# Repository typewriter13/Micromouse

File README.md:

# Micromouse

MicroMouse is a small autonomous robot designed to navigate and solve a maze completely on its own.

## About The Project

Our project is about a wall-following micromouse robot built on ESP32-S3, using IR proximity sensors for wall-centering and junction detection, a VL53L0X ToF sensor for front-wall stopping, quadrature encoders for wheel feedback, and a WiFi-based web UI for live tuning of PID gains, thresholds, and duty cycle limits.

https://github.com/user-attachments/assets/4806b698-6c4b-4d95-9de0-e866a1863b37

## Project Overview

### Hardware Used
- 1x ESP32-S3
- 1x DRV8833 Motor Driver
- 1x AMS1117 LDO
- 1x TPS54302 Buck Converter
- 2x DC encoder Motors
- 4x IR sensors
- 1x VL53L0X (Time of flight sensor)

### Pinout Mapping

| Component | Function / Pin | ESP32-S3 GPIO |
| :--- | :--- | :--- |
| **ToF Sensor** | I2C SDA / SCL | GPIO 41 / GPIO 42 |
| **IR Right (`IR_PIN_0`)** | ADC Input | ADC1 CH2 GPIO 3 |
| **IR Left (`IR_PIN_1`)** | ADC Input | ADC1 CH8 GPIO 9|
| **IR Left Diag (`IR_PIN_2`)** | ADC Input | ADC1 CH9 GPIO 10|
| **IR Right Diag (`IR_PIN_3`)**| ADC Input | ADC1 CH7 GPIO 8|
| **Encoder Motors** | Channel A | GPIO 4 / GPIO 5 |
| **Encoder Motors** | Channel B | GPIO 6 / GPIO 7 |

# Repository Structure

Each subdirectory has its own README with details specific to that piece:

| Directory | Contents |
| :--- | :--- |
| [`LeftWallFollow`](LeftWallFollow/README.md) | Full left-hand-follow navigation, PD wall-centering, ToF stopping, WiFi live tuning |
| [`Test-Codes`](Test-Codes/README.md) | Reference codes for development stages along the project |
| [`PCB`](PCB/README.md) | KiCad schematic and board layout |

## CAD and PCB Models

### PCB Model

### CAD Models

## Installation and Setup

Prerequisites:
1. ESP-IDF v5.5 
2. Git
3. Python 3.10 or higher

**Setup:**
1. **Clone the Repository**
   ```bash
   git clone https://github.com/typewriter13/Micromouse
   cd Micromouse
   cd LeftWallFollow
2. **Configure and Build**
   ```bash
   idf.py set-target esp32s3
   idf.py build
3. **Flashing the Project**
   ```bash
   idf.py flash monitor

## Future Work

- Implementing Left hand Follow algorithm tuned according to the Maze which we have designed.
- Work and study many more algorithms which are more efficient than LHF.
- Integrate the encoder readings with our path calculations of the bot for mapping the maze and reading the distance travelled.

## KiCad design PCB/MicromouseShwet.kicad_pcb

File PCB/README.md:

# PCB

KiCad design for the micromouse's custom PCB

| File | Contents |
| :--- | :--- |
| `MicromouseProject.kicad_pro` | KiCad project file — open this first |
| `MicromouseSch.kicad_sch` | Schematic |
| `MicromousePCB.kicad_pcb` | PCB layout/routing |

Rendered schematic and board images are in [`Assets`](../Assets/) and shown in the [top-level README](../README.md#cad-and-pcb-models).

Requires [KiCad](https://www.kicad.org/) to open and edit.

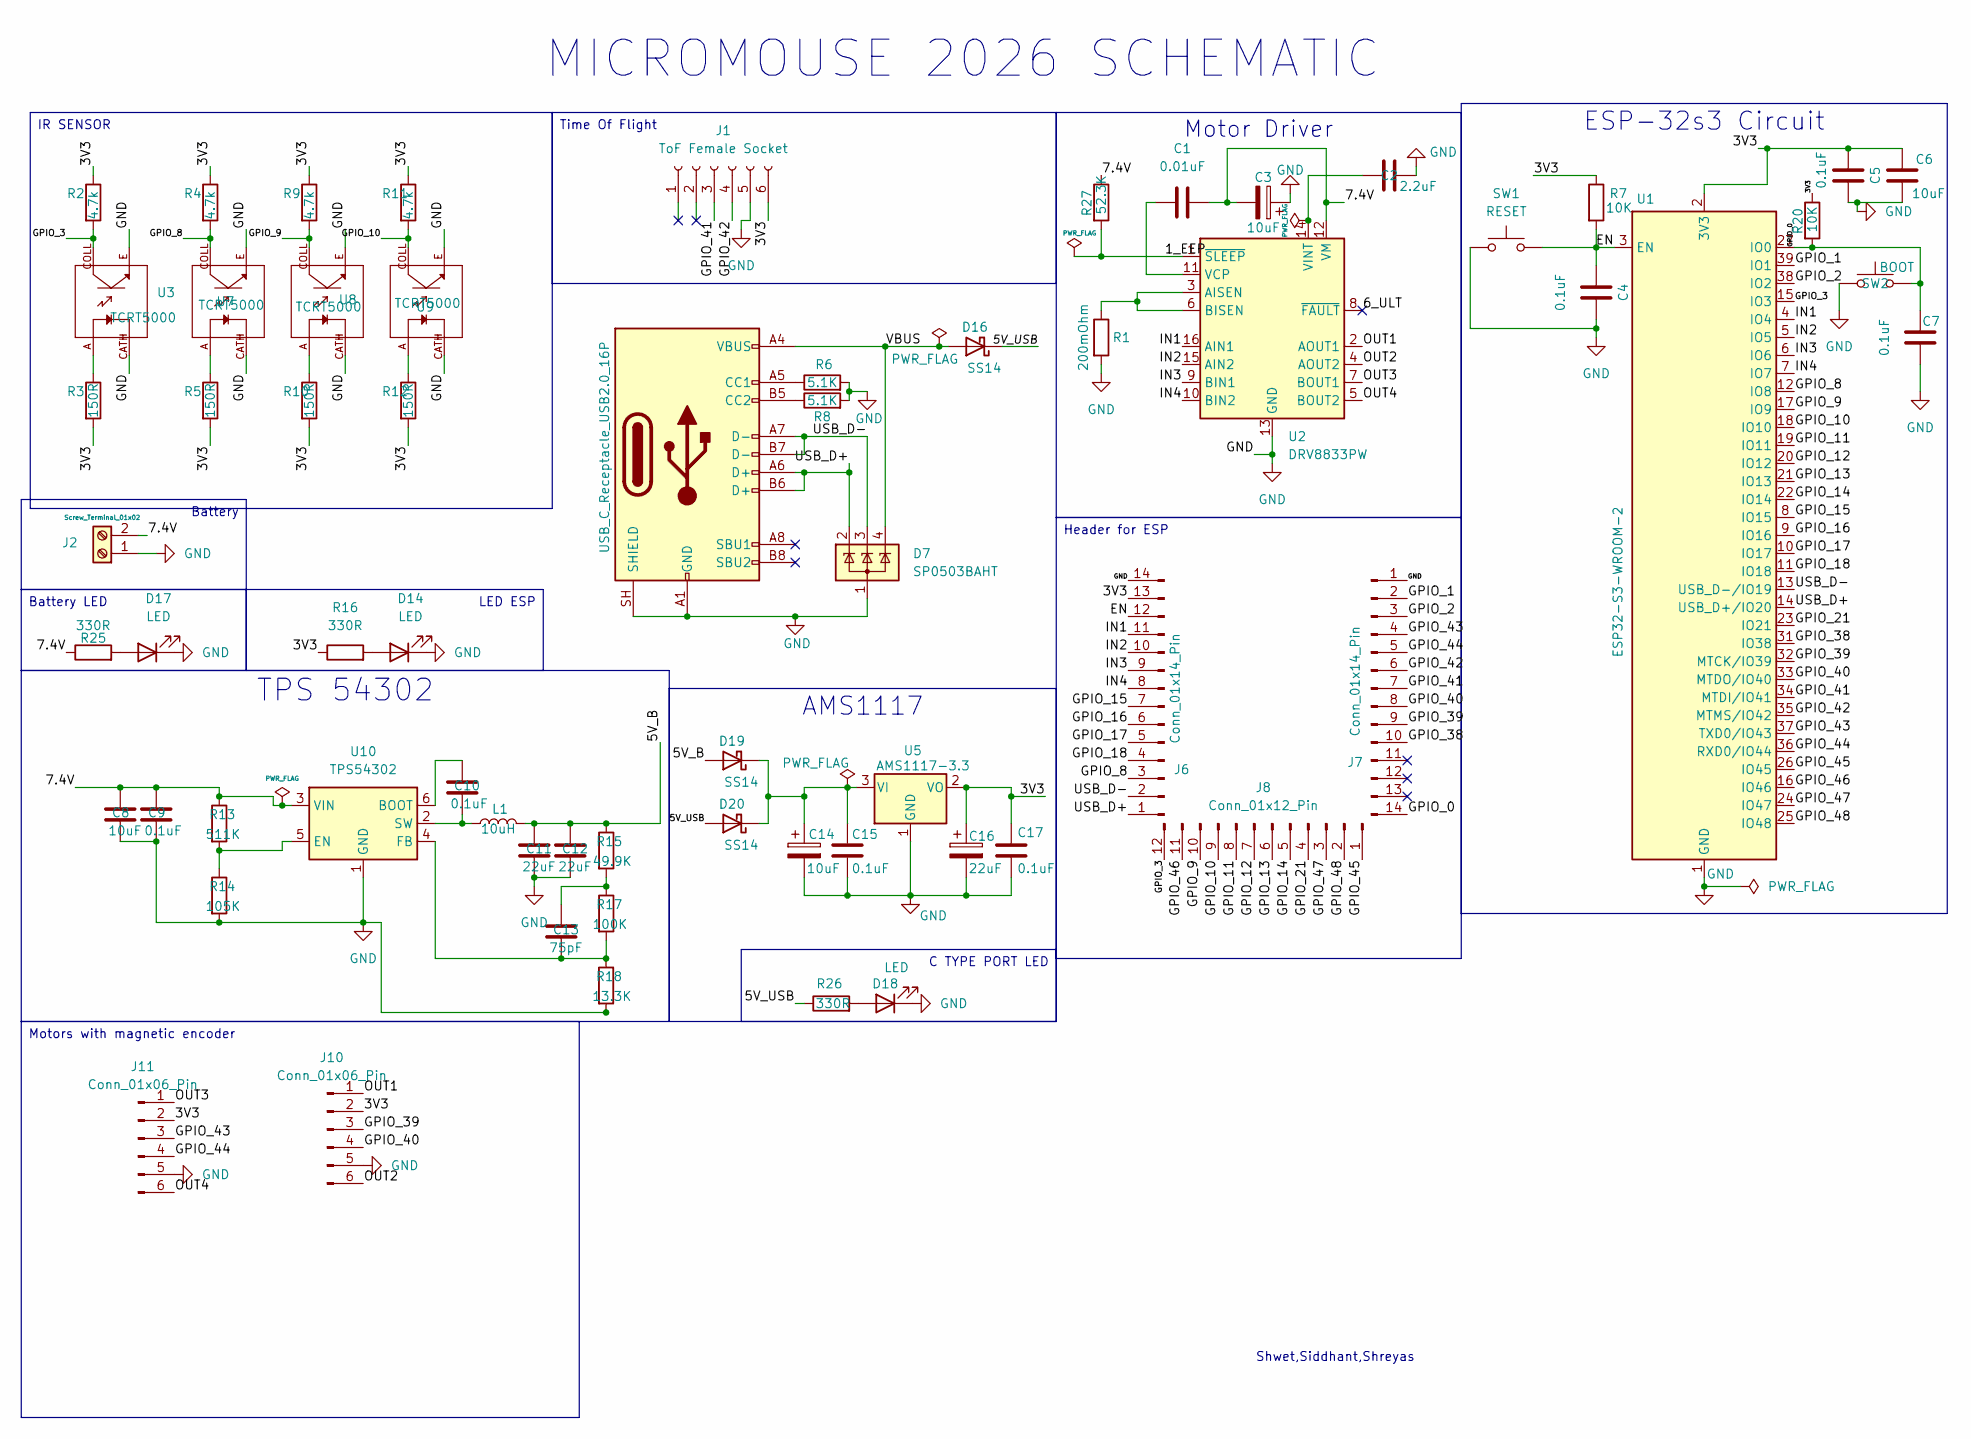
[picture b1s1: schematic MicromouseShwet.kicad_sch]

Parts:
C1: 0.01uF; C_0805_2012Metric
C2: 2.2uF; C_0805_2012Metric
C3, C6, C8, C14: 10uF; C_0805_2012Metric
C4, C5, C7, C9, C10, C15, C17: 0.1uF; C_0805_2012Metric
C11, C12, C16: 22uF; C_0805_2012Metric
C13: 75pF; C_0805_2012Metric
D7: SP0503BAHT; SOT-143
D14, D17, D18: LED; LED_0805_2012Metric
D16, D19, D20: SS14; D_SMA
J1: ToF Female Socket; PinSocket_1x06_P2.54mm_Vertical
J2: Screw_Terminal_01x02; JST_EH_S2B-EH_1x02_P2.50mm_Horizontal
J5: USB_C_Receptacle_USB2.0_16P; USB_C_Receptacle_GCT_USB4105-xx-A_16P_TopMnt_Horizontal
J6, J7: Conn_01x14_Pin; PinHeader_1x14_P1.27mm_Vertical
J8: Conn_01x12_Pin; PinHeader_1x12_P1.27mm_Vertical
J10, J11: Conn_01x06_Pin; JST_ZH_B6B-ZR_1x06_P1.50mm_Vertical
L1: 10uH; L_Sunlord_MWSA0603S
R1: 200mOhm; R_0805_2012Metric
R2, R4, R9, R11: 4.7k; R_0805_2012Metric
R3, R5, R10, R12: 150R; R_0805_2012Metric
R6, R8: 5.1K; R_0805_2012Metric
R7, R20: 10K; R_0805_2012Metric
R13: 511K; R_0805_2012Metric
R14: 105K; R_0805_2012Metric
R15: 49.9K; R_0805_2012Metric
R16, R25, R26: 330R; R_0805_2012Metric
R17: 100K; R_0805_2012Metric
R18: 13.3K; R_0805_2012Metric
R27: 52.3K; R_0805_2012Metric
SW1: RESET; SW_Push_SPST_NO_Alps_SKRK
SW2: BOOT; SW_Push_SPST_NO_Alps_SKRK
U1: ESP32-S3-WROOM-2
U2: DRV8833PW; TSSOP-16_4.4x5mm_P0.65mm
U3, U7, U8, U9: TCRT5000; OPTO_TCRT5000; PARTREV 1.7
U5: AMS1117-3.3; SOT-223-3_TabPin2
U10: TPS54302; SOT-23-6

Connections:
/1_EEP: R27.2, U2.1 (~SLEEP)
/3V3: C5.2, C6.1, C16.1, C17.1, J1.6, J6.13, J10.2, J11.2, R2.1, R3.2, R4.1, R5.2, R7.1, R9.1, R10.2, R11.1, R12.2, R16.1, R20.1, U1.2 (3V3), U5.2 (VO)
/5V_B: C11.1, C12.1, D19.2 (A), L1.2, R15.1
/5V_USB: D16.1 (K), D20.2 (A), R26.1
/6_ULT: U2.8 (~FAULT)
/7.4V: C1.2, C3.2, C8.1, C9.1, J2.2, R13.1, R25.1, R27.1, U2.12 (VM), U10.3 (VIN)
/EN: C4.2, J6.12, R7.2, SW1.2, U1.3 (EN)
/GPIO_0: C7.2, J7.14, R20.2, SW2.2, U1.27 (IO0)
/GPIO_1: J7.2, U1.39 (IO1)
/GPIO_2: J7.3, U1.38 (IO2)
/GPIO_3: J8.12, R2.2, U1.15 (IO3), U3.COLL
/GPIO_8: J6.3, R4.2, U1.12 (IO8), U7.COLL
/GPIO_9: J8.10, R9.2, U1.17 (IO9), U8.COLL
/GPIO_10: J8.9, R11.2, U1.18 (IO10), U9.COLL
/GPIO_11: J8.8, U1.19 (IO11)
/GPIO_12: J8.7, U1.20 (IO12)
/GPIO_13: J8.6, U1.21 (IO13)
/GPIO_14: J8.5, U1.22 (IO14)
/GPIO_15: J6.7, U1.8 (IO15)
/GPIO_16: J6.6, U1.9 (IO16)
/GPIO_17: J6.5, U1.10 (IO17)
/GPIO_18: J6.4, U1.11 (IO18)
/GPIO_21: J8.4, U1.23 (IO21)
/GPIO_38: J7.10, U1.31 (IO38)
/GPIO_39: J7.9, J10.3, U1.32 (MTCK/IO39)
/GPIO_40: J7.8, J10.4, U1.33 (MTDO/IO40)
/GPIO_41: J1.3, J7.7, U1.34 (MTDI/IO41)
/GPIO_42: J1.4, J7.6, U1.35 (MTMS/IO42)
/GPIO_43: J7.4, J11.3, U1.37 (TXD0/IO43)
/GPIO_44: J7.5, J11.4, U1.36 (RXD0/IO44)
/GPIO_45: J8.1, U1.26 (IO45)
/GPIO_46: J8.11, U1.16 (IO46)
/GPIO_47: J8.3, U1.24 (IO47)
/GPIO_48: J8.2, U1.25 (IO48)
/IN1: J6.11, U1.4 (IO4), U2.16 (AIN1)
/IN2: J6.10, U1.5 (IO5), U2.15 (AIN2)
/IN3: J6.9, U1.6 (IO6), U2.9 (BIN1)
/IN4: J6.8, U1.7 (IO7), U2.10 (BIN2)
/OUT1: J10.1, U2.2 (AOUT1)
/OUT2: J10.6, U2.4 (AOUT2)
/OUT3: J11.1, U2.7 (BOUT1)
/OUT4: J11.6, U2.5 (BOUT2)
/USB_D+: D7.2 (K), J5.A6 (D+), J5.B6 (D+), J6.1, U1.14 (USB_D+/IO20)
/USB_D-: D7.3 (K), J5.A7 (D-), J5.B7 (D-), J6.2, U1.13 (USB_D-/IO19)
/VBUS: D7.4 (K), D16.2 (A), J5.A4 (VBUS), J5.A9 (VBUS), J5.B4 (VBUS), J5.B9 (VBUS)
GND: C2.2, C3.1, C4.1, C5.1, C6.2, C7.1, C8.2, C9.2, C11.2, C12.2, C14.2, C15.2, C16.2, C17.2, D7.1 (A), D14.1 (K), D17.1 (K), D18.1 (K), J1.5, J2.1, J5.A1 (GND), J5.A12 (GND), J5.B1 (GND), J5.B12 (GND), J5.SH (SHIELD), J6.14, J7.1, J10.5, J11.5, R1.2, R6.2, R8.2, R14.2, R18.2, SW1.1, SW2.1, U1.1 (GND), U1.40 (GND), U1.41 (GND), U2.13 (GND), U3.CATH, U3.E, U5.1 (GND), U7.CATH, U7.E, U8.CATH, U8.E, U9.CATH, U9.E, U10.1 (GND)
unnamed: C13.1, R15.2, R17.1
unnamed: D14.2 (A), R16.2
unnamed: D17.2 (A), R25.2
unnamed: D18.2 (A), R26.2
unnamed: C14.1, C15.1, D19.1 (K), D20.1 (K), U5.3 (VI)
unnamed: J5.A5 (CC1), R6.1
unnamed: J5.B5 (CC2), R8.1
unnamed: R3.1, U3.A
unnamed: R5.1, U7.A
unnamed: R10.1, U8.A
unnamed: R12.1, U9.A
unnamed: R1.1, U2.3 (AISEN), U2.6 (BISEN)
unnamed: C1.1, U2.11 (VCP)
unnamed: C2.1, U2.14 (VINT)
unnamed: C10.1, U10.6 (BOOT)
unnamed: R13.2, R14.1, U10.5 (EN)
unnamed: C13.2, R17.2, R18.1, U10.4 (FB)
unnamed: C10.2, L1.1, U10.2 (SW)

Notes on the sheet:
MICROMOUSE 2026 SCHEMATIC
Shwet,Siddhant,Shreyas
Motors with magnetic encoder
ESP-32s3 Circuit
LED ESP
IR SENSOR
Battery LED
AMS1117
TPS 54302
Header for ESP
Battery
C TYPE PORT LED
Motor Driver
Time Of Flight

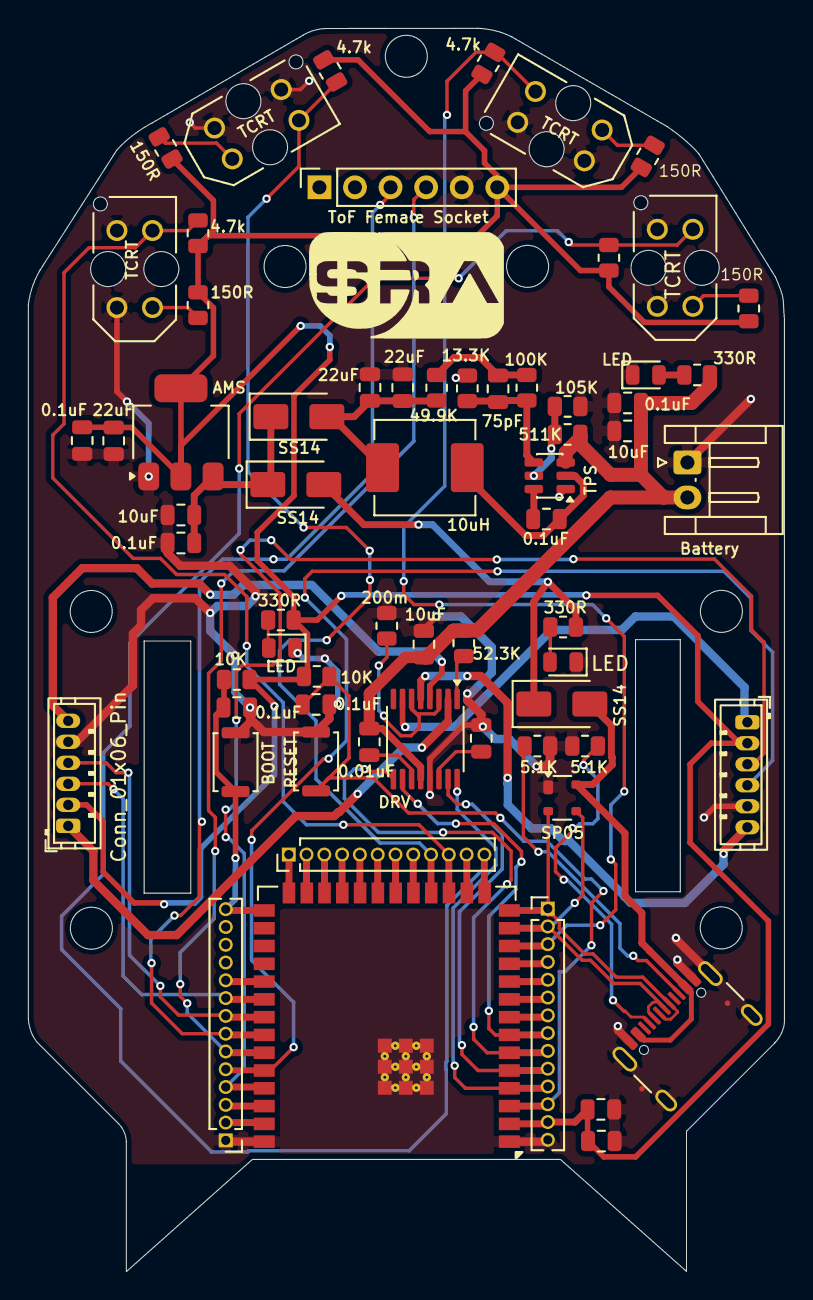
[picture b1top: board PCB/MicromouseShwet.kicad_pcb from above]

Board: 2 copper layers, 54.0 x 88.8 mm, 65 parts (0 on the bottom side), 63 nets.

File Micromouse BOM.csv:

"Reference","Qty","Value","DNP","Exclude from BOM","Exclude from Board","Footprint","Datasheet"
"C1","1","0.01uF","","","","Capacitor_SMD:C_0805_2012Metric","https://robu.in/product/c0805c103k3ractu-kemet-smd-multilaye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"
"C2","1","2.2uF","","","","Capacitor_SMD:C_0805_2012Metric","https://robu.in/product/c2012x7r1h225k125ae-tdk-smd-multilay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"
"C3,C6,C8,C14","4","10uF","","","","Capacitor_SMD:C_0805_2012Metric","https://evelta.com/10uf-25v-10-x7r-0805-mlcc-multilayer-cera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"
"C4,C5,C7,C9,C10,C15,C17","7","0.1uF","","","","Capacitor_SMD:C_0805_2012Metric","https://robu.in/product/c0805c104k1ractu-kemet-smd-multilaye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"
"C11,C12,C16","3","22uF","","","","Capacitor_SMD:C_0805_2012Metric","https://www.ktron.in/product/22uf-25v-ceramic-capacitor-smd-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"
"C13","1","75pF","","","","Capacitor_SMD:C_0805_2012Metric","https://robu.in/product/tcc0805cog750j500bt-cctc-smt-ceramic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"
"D7","1","SP0503BAHT","","","","Package_TO_SOT_SMD:SOT-143","https://robu.in/product/sp0503bahtg-littelfuse-sp0503bahtg-e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"
"D14,D17,D18","3","LED","","","","LED_SMD:LED_0805_2012Metric","https://robu.in/product/17-21-g6c-ap1q1b-3t-everlight-yellow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"
"D16,D19,D20","3","SS14","","","","Diode_SMD:D_SMA","https://robu.in/product/ss14-slkor-40v-550mv1a-1a-smado-214a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"
"J1","1","ToF Female Socket","","","","Connector_PinSocket_2.54mm:PinSocket_1x06_P2.54mm_Vertical","https://robu.in/product/6-pin-female-11mm-tall-stackable-hea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"
"J2","1","Screw_Terminal_01x02","","","","Connector_JST:JST_EH_S2B-EH_1x02_P2.50mm_Horizontal","https://robu.in/product/2-pin-2-54mm-pitch-pluggable-screw-t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"
"J5","1","USB_C_Receptacle_USB2.0_16P","","","","Connector_USB:USB_C_Receptacle_GCT_USB4105-xx-A_16P_TopMnt_Horizontal","https://evelta.com/usb-type-c-receptacle-vertical-mount-usb-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"
"J6,J7","2","Conn_01x14_Pin","","","","Connector_PinHeader_1.27mm:PinHeader_1x14_P1.27mm_Vertical","https://robu.in/product/1-27mm-1x40-pin-male-single-row-head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"
"J8","1","Conn_01x12_Pin","","","","Connector_PinHeader_1.27mm:PinHeader_1x12_P1.27mm_Vertical","https://robu.in/product/1-27mm-1x40-pin-male-single-row-head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"
"J10,J11","2","Conn_01x06_Pin","","","","Connector_JST:JST_ZH_B6B-ZR_1x06_P1.50mm_Vertical","https://robu.in/product/b6b-xh-alfsn-jst-1x6p-6p-xh-tin-6-25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"
"L1","1","10uH","","","","Inductor_SMD:L_Sunlord_MWSA0603S","https://robu.in/product/mwsa0603s-100mt-sunlord-10uh-5-2a-20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"
"R1","1","200mOhm","","","","Resistor_SMD:R_0805_2012Metric","https://evelta.com/200e-5-0805-smd-resistor-royal-ohm-0805s8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"
"R2,R4,R9,R11","4","4.7k","","","","Resistor_SMD:R_0805_2012Metric","https://robu.in/product/wr08x472jtl-walsin-125mw-thick-film-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"
"R3,R5,R10,R12","4","150R","","","","Resistor_SMD:R_0805_2012Metric","https://robu.in/product/ac0805fr-07150rl-yageo-res-thick-fil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"
"R6,R8","2","5.1K","","","","Resistor_SMD:R_0805_2012Metric","https://robu.in/product/erj6geyj512v-panasonic-125mw-thick-f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"
"R7,R20","2","10K","","","","Resistor_SMD:R_0805_2012Metric","https://robu.in/product/ac0805fr-0710kl-yageo-res-thick-film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"
"R13","1","511K","","","","Resistor_SMD:R_0805_2012Metric","https://robu.in/product/ac0805fr-07511kl-yageo-125mw-thick-f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"
"R14","1","105K","","","","Resistor_SMD:R_0805_2012Metric","https://robu.in/product/rc0805fr-07105kl-yageo-125mw-thick-f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"
"R15","1","49.9K","","","","Resistor_SMD:R_0805_2012Metric","https://robu.in/product/crcw080549k9fkea-vishay-intertech-12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"
"R16,R25,R26","3","330R","","","","Resistor_SMD:R_0805_2012Metric","https://robu.in/product/rc0805fr-07330rl-yageo-res-thick-fil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"
"R17","1","100K","","","","Resistor_SMD:R_0805_2012Metric","https://robu.in/product/ac0805fr-7w100kl-yageo-res-thick-fil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"
"R18","1","13.3K","","","","Resistor_SMD:R_0805_2012Metric","https://robu.in/product/rc0805fr-0713k3l-yageo-125mw-thick-f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"
"R27","1","52.3K","","","","Resistor_SMD:R_0805_2012Metric","https://robu.in/product/ac0805fr-0752k3l-yageo-125mw-thick-f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"
"SW1","1","RESET","","","","Button_Switch_SMD:SW_Push_SPST_NO_Alps_SKRK","https://www.ktron.in/product/3x4x2mm-smd-tactile-switch/?srs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"
"SW2","1","BOOT","","","","Button_Switch_SMD:SW_Push_SPST_NO_Alps_SKRK","https://www.ktron.in/product/3x4x2mm-smd-tactile-switch/?srs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"
"U1","1","ESP32-S3-WROOM-2","","","","RF_Module:ESP32-S3-WROOM-2","https://mou.sr/45h7VjL"
"U2","1","DRV8833PW","","","","Package_SO:TSSOP-16_4.4x5mm_P0.65mm","https://www.lioncircuits.com/parts/DRV8833PW?srsltid=AfmBOoq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"
"U3,U7,U8,U9","4","TCRT5000","","","","TCRT5000:OPTO_TCRT5000","https://robu.in/product/tcrt5000-reflective-ir-sensor-photoe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"
"U5","1","AMS1117-3.3","","","","Package_TO_SOT_SMD:SOT-223-3_TabPin2","https://evelta.com/ams1117-3-3-linear-voltage-regulator-3-3v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"
"U10","1","TPS54302","","","","Package_TO_SOT_SMD:SOT-23-6","https://robu.in/product/tps54302ddcr-texas-instruments-step-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"

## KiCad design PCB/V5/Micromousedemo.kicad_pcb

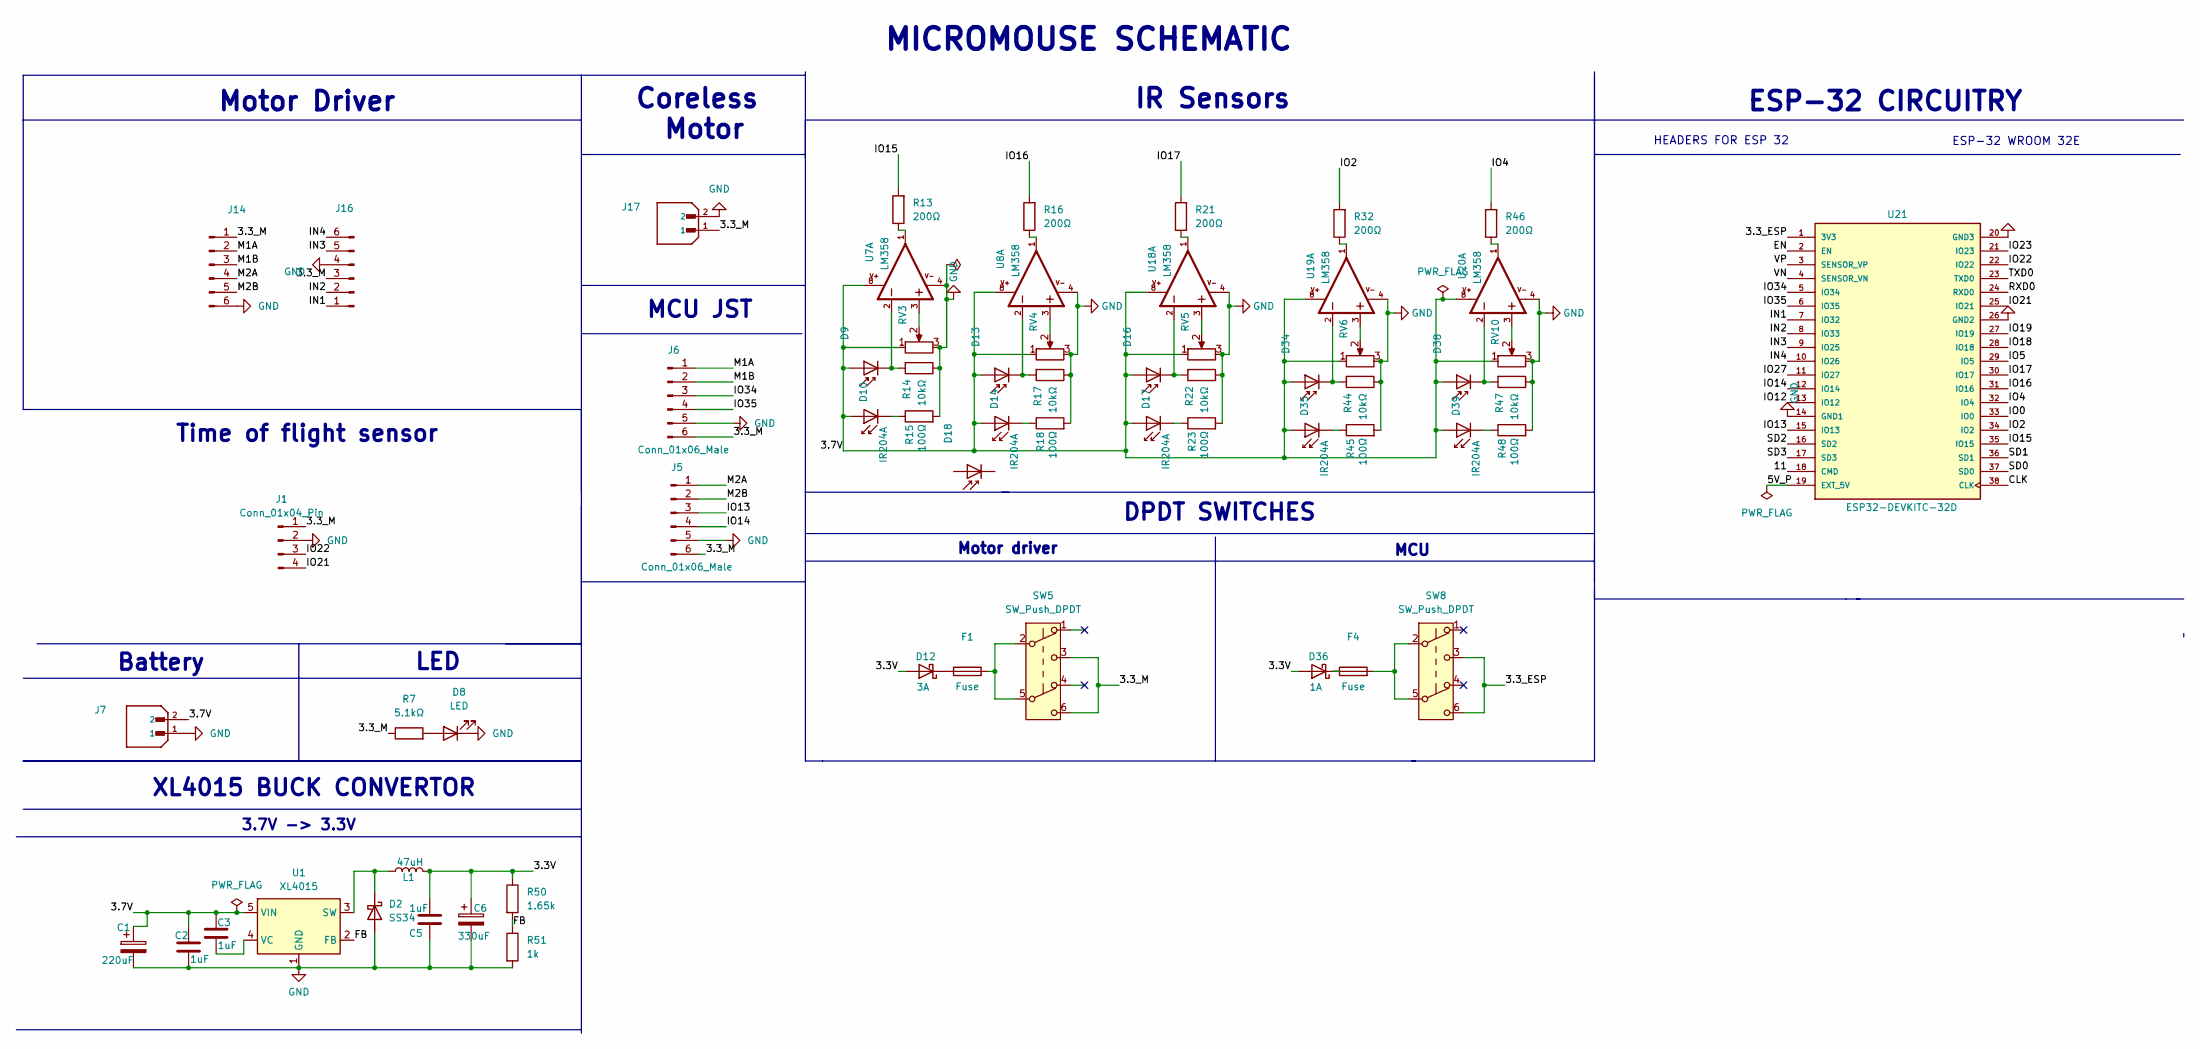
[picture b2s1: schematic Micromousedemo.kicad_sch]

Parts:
C1: 220uF; CP_Elec_6.3x7.7
C2, C3, C5: 1uF; C_0603_1608Metric
C6: 330uF; CP_Elec_8x10.5
D2: SS34; D_SMA
D8: LED; LED_0603_1608Metric
D9, D13, D16, D18, D34, D38: D_Photo; LED2-2.54-D5.0MM
D10, D14, D17, D35, D39: IR204A; LED_D3.0mm_IRBlack
D12: 3A; D_SMB
D36: 1A; D_SMA
F1, F4: Fuse; RUEF160
J1: Conn_01x04_Pin; PinHeader_1x04_P2.54mm_Vertical
J5, J6: Conn_01x06_Male; PinHeader_1x06_P2.54mm_Vertical
J7, J17: B2B-XH-A_LF__SN_; JST_B2B-XH-A_LF__SN_; PARTREV N/A
J14, J16: Conn_01x06_Pin; PinHeader_1x06_P2.54mm_Vertical
L1: 47uH; L_10.4x10.4_H4.8
R7: 5.1kΩ; R_0603_1608Metric
R13, R16, R21, R32, R46: 200Ω; R_0603_1608Metric
R14, R17, R22, R44, R47: 10kΩ; R_0603_1608Metric
R15, R18, R23, R45, R48: 100Ω; R_0603_1608Metric
R50: 1.65k; R_0603_1608Metric
R51: 1k; R_0603_1608Metric
RV3, RV4, RV5, RV6, RV10: R_Potentiometer; TRIM_3362P-1-253LF123
SW5, SW8: SW_Push_DPDT; SW_TL2230OAF140
U1: XL4015; TO-263-5_TabPin3
U7, U8, U18, U19, U20: LM358; SOIC8_150MIL
U21: ESP32-DEVKITC-32D; MODULE_ESP32-DEVKITC-32D; PARTREV 4

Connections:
/3.3V: C5.1, C6.1, D12.2 (A), D36.2 (A), L1.2, R50.1
/3.3_ESP: SW8.3 (C), SW8.6 (C), U21.1 (3V3)
/3.3_M: J1.1, J5.6, J6.6, J14.1, J16.3, J17.1, R7.1, SW5.3 (C), SW5.6 (C)
/3.7V: C1.1, C2.1, C3.1, D9.2 (A), D10.2 (A), D13.2 (A), D14.2 (A), D16.2 (A), D17.2 (A), D34.2 (A), D35.2 (A), D38.2 (A), D39.2 (A), J7.2, RV3.1, RV4.1, RV5.1, RV6.1, RV10.1, U1.5 (VIN), U7.8, U8.8, U18.8, U19.8, U20.8
/5V_P: U21.19 (EXT_5V)
/11: U21.18 (CMD)
/CLK: U21.38 (CLK)
/EN: U21.2 (EN)
/FB: R50.2, R51.1, U1.2 (FB)
/IN1: J16.1, U21.7 (IO32)
/IN2: J16.2, U21.8 (IO33)
/IN3: J16.5, U21.9 (IO25)
/IN4: J16.6, U21.10 (IO26)
/IO0: U21.33 (IO0)
/IO2: R32.2, U21.34 (IO2)
/IO4: R46.2, U21.32 (IO4)
/IO5: U21.29 (IO5)
/IO12: U21.13 (IO12)
/IO13: J5.3, U21.15 (IO13)
/IO14: J5.4, U21.12 (IO14)
/IO15: R13.2, U21.35 (IO15)
/IO16: R16.2, U21.31 (IO16)
/IO17: R21.2, U21.30 (IO17)
/IO18: U21.28 (IO18)
/IO19: U21.27 (IO19)
/IO21: J1.4, U21.25 (IO21)
/IO22: J1.3, U21.22 (IO22)
/IO23: U21.21 (IO23)
/IO27: U21.11 (IO27)
/IO34: J6.3, U21.5 (IO34)
/IO35: J6.4, U21.6 (IO35)
/M1A: J6.1, J14.2
/M1B: J6.2, J14.3
/M2A: J5.1, J14.4
/M2B: J5.2, J14.5
/RXD0: U21.24 (RXD0)
/SD0: U21.37 (SD0)
/SD1: U21.36 (SD1)
/SD2: U21.16 (SD2)
/SD3: U21.17 (SD3)
/TXD0: U21.23 (TXD0)
/VN: U21.4 (SENSOR_VN)
/VP: U21.3 (SENSOR_VP)
GND: C1.2, C2.2, C5.2, C6.2, D2.2 (A), D8.1 (K), J1.2, J5.5, J6.5, J7.1, J14.6, J16.4, J17.2, R14.1, R15.2, R17.1, R18.2, R22.1, R23.2, R44.1, R45.2, R47.1, R48.2, R51.2, RV3.3, RV4.3, RV5.3, RV6.3, RV10.3, U1.1 (GND), U7.4, U8.4, U18.4, U19.4, U20.4, U21.14 (GND1), U21.20 (GND3), U21.26 (GND2)
unnamed: D2.1 (K), L1.1, U1.3 (SW)
unnamed: D8.2 (A), R7.2
unnamed: D9.1 (K), R14.2, U7.2
unnamed: D10.1 (K), R15.1
unnamed: D12.1 (K), F1.1
unnamed: D13.1 (K), R17.2, U8.2
unnamed: D14.1 (K), R18.1
unnamed: D16.1 (K), R22.2, U18.2
unnamed: D17.1 (K), R23.1
unnamed: D34.1 (K), R44.2, U19.2
unnamed: D35.1 (K), R45.1
unnamed: D36.1 (K), F4.1
unnamed: D38.1 (K), R47.2, U20.2
unnamed: D39.1 (K), R48.1
unnamed: F1.2, SW5.2 (B), SW5.5 (B)
unnamed: F4.2, SW8.2 (B), SW8.5 (B)
unnamed: R13.1, U7.1
unnamed: R16.1, U8.1
unnamed: R21.1, U18.1
unnamed: R32.1, U19.1
unnamed: R46.1, U20.1
unnamed: RV3.2, U7.3
unnamed: RV4.2, U8.3
unnamed: RV5.2, U18.3
unnamed: RV6.2, U19.3
unnamed: RV10.2, U20.3
unnamed: C3.2, U1.4 (VC)

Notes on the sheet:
Coreless Motor
MICROMOUSE SCHEMATIC
ESP-32 WROOM 32E
Battery
ESP-32 CIRCUITRY
DPDT SWITCHES
IR Sensors
MCU JST
3.7V -> 3.3V
HEADERS FOR ESP 32
MCU
XL4015 BUCK CONVERTOR
Motor driver
LED
Time of flight sensor
Motor Driver

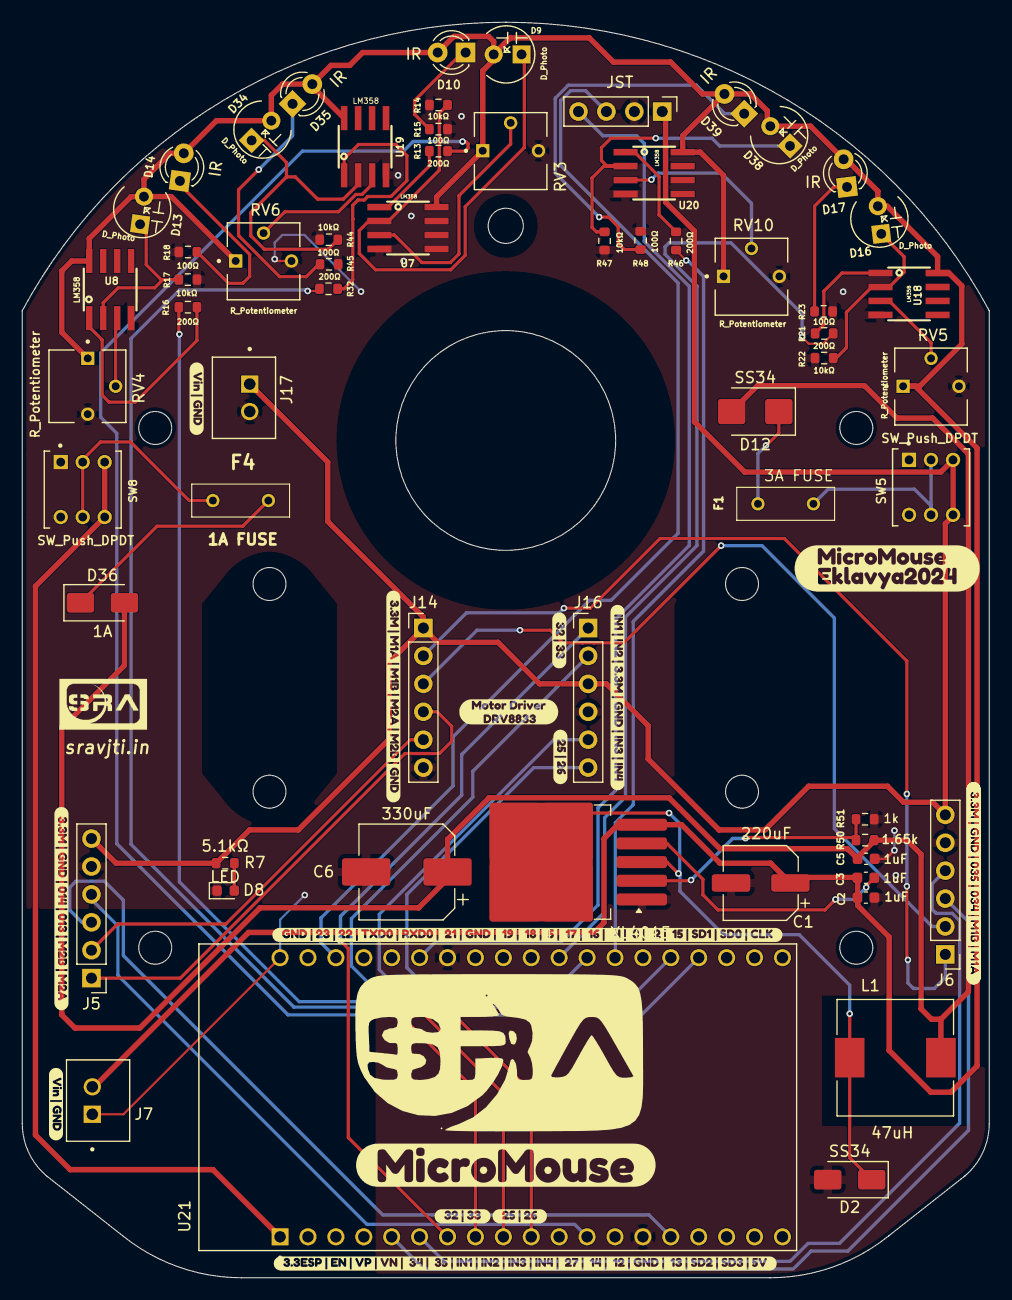
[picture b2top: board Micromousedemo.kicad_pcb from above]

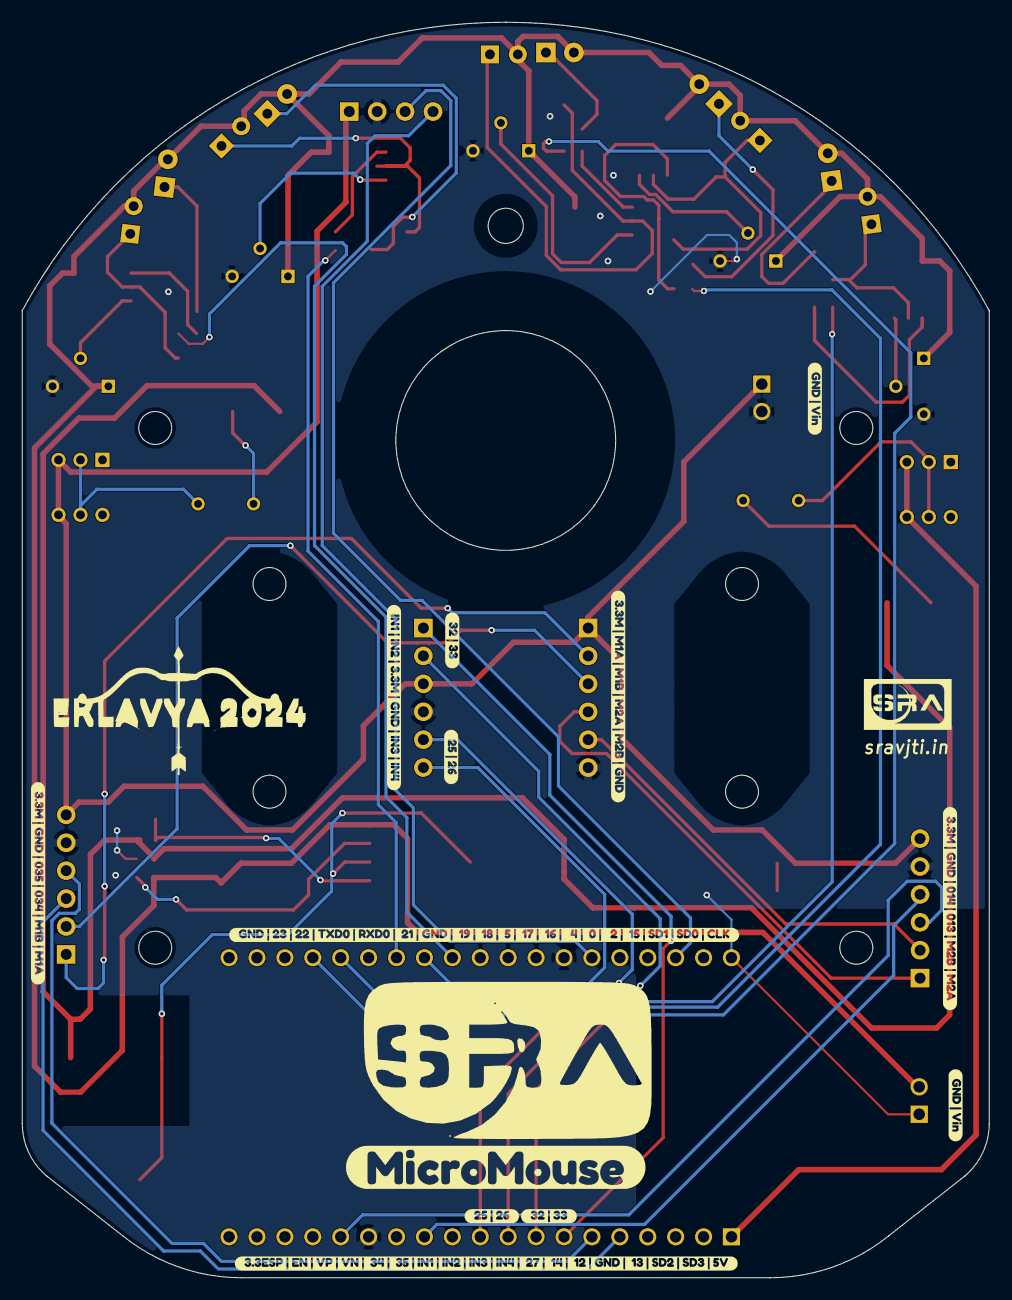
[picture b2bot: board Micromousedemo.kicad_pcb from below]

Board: 2 copper layers, 88.0 x 114.3 mm, 90 parts (13 on the bottom side), 52 nets.

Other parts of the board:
kibuzzard-66C4A04A, kibuzzard-66C4A04A#2: G***; kibuzzard-66C4A04A
kibuzzard-66C4A074, kibuzzard-66C4A074#2: G***; kibuzzard-66C4A074
kibuzzard-66C49AF5, kibuzzard-66C49AF5#2, kibuzzard-66C49AF5#3, kibuzzard-66C49AF5#4: G***; kibuzzard-66C49AF5
kibuzzard-66C49BB8, kibuzzard-66C49BB8#2: G***; kibuzzard-66C49BB8
kibuzzard-66C49C11, kibuzzard-66C49C11#2: G***; kibuzzard-66C49C11
kibuzzard-66C49C59, kibuzzard-66C49C59#2, kibuzzard-66C49C59#3, kibuzzard-66C49C59#4: G***; kibuzzard-66C49C59
kibuzzard-66C308A6: G***; kibuzzard-66C308A6
kibuzzard-66C486A2, kibuzzard-66C486A2#2: G***; kibuzzard-66C486A2
kibuzzard-66C2808F: G***; kibuzzard-66C2808F
kibuzzard-66C28409: G***; kibuzzard-66C28409
kibuzzard-66C30793, kibuzzard-66C30793#2: G***; kibuzzard-66C30793
kibuzzard-66C30870: G***; kibuzzard-66C30870
kibuzzard-66C31908, kibuzzard-66C31908#2: G***; kibuzzard-66C31908
kibuzzard-66C31993, kibuzzard-66C31993#2, kibuzzard-66C31993#3: G***; kibuzzard-66C31993
